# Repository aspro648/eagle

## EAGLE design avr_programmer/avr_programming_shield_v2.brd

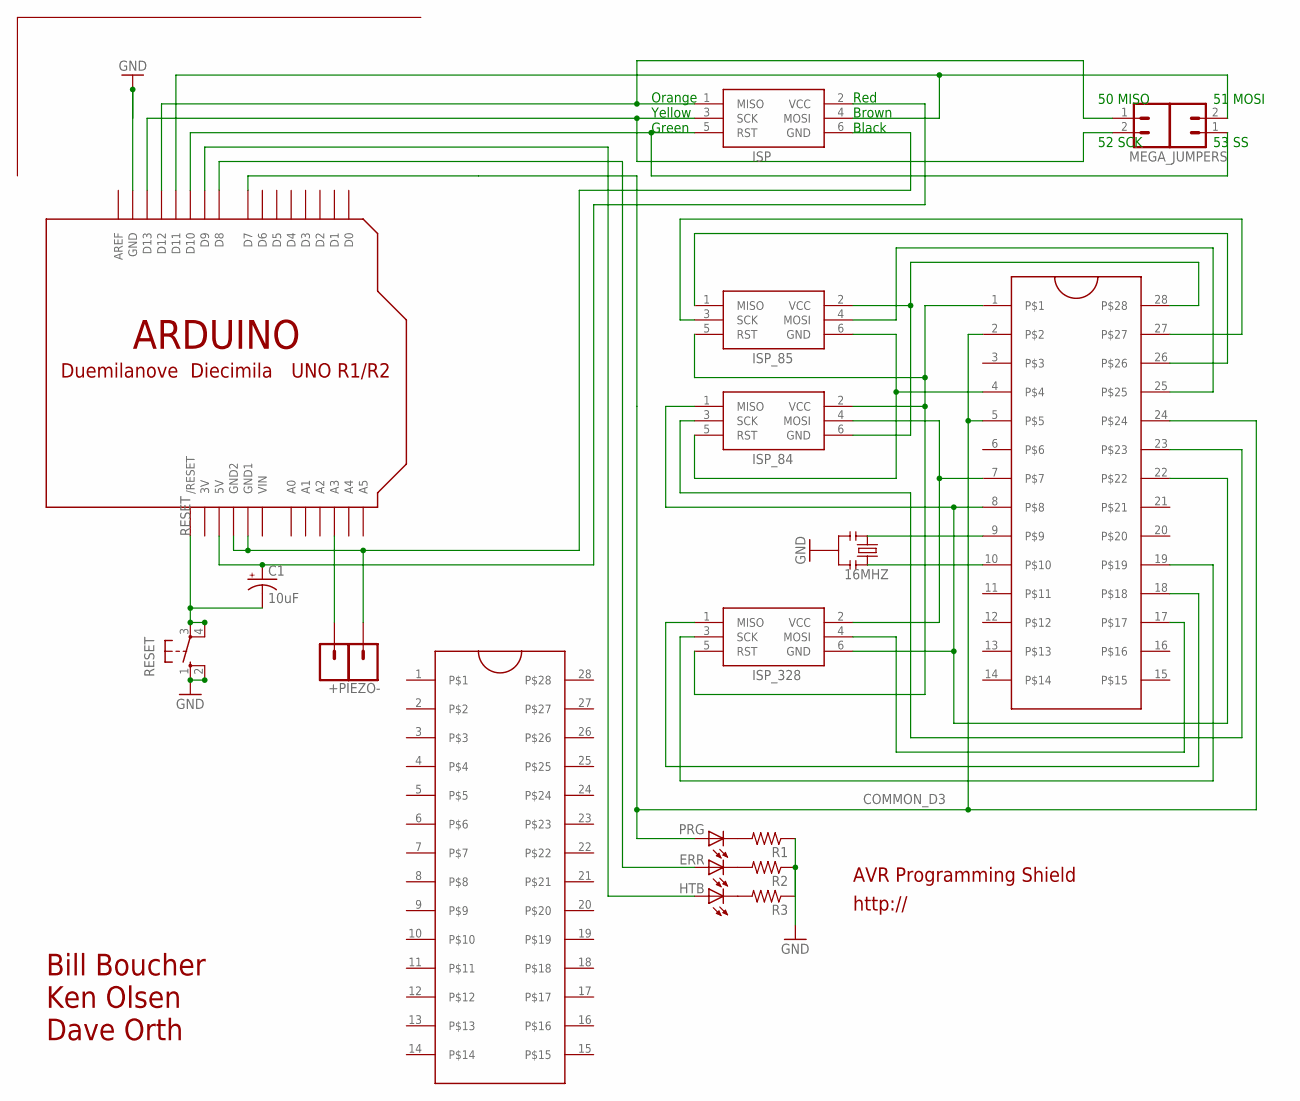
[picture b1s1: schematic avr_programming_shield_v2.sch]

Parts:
16MHZ: RESONATORPTH; RESONATOR-PTH
+PIEZO-: M01PTH; 1X01
C1: 10uF; CPOL-RADIAL-10UF-25V; MPN 106TTA035M
ERR: LED3MM
HTB: LED3MM
ISP: AVRISP-6; AVRISP
ISP_84, ISP_85, ISP_328: AVRISP-6; AVRISP
JP2: M02PTH; 1X02
JP4: M01PTH; 1X01
MEGA_JUMPERS: M02PTH; 1X02
PRG: LED3MM
R1, R2, R3: R-US_0204/2V; 0204V
RESET: 10-XX; B3F-10XX; MPN B3F-1000
U$1: ARDUINO-NOHOLE
U$3, U$4: ZIFSOCKET-28-3ZIFFSOCKET-28-3; DIL28-3-ZIF_SOCKET

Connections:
3V: U$1.3V
COMMON_D3: PRG.A, U$1.D7, U$4.2, U$4.5, U$4.24
GND: 16MHZ.2, +PIEZO-.1, ISP.6 (GND), R1.1, R2.1, R3.1, RESET.1 (S), RESET.2 (S1), U$1.GND, U$1.GND1, U$1.GND2
unnamed: ISP_328.4 (MOSI), U$4.17
unnamed: ISP.3 (SCK), MEGA_JUMPERS.2, U$1.D13
unnamed: ISP.1 (MISO), MEGA_JUMPERS.1, U$1.D12
unnamed: ISP_328.1 (MISO), U$4.18
unnamed: ISP.5 (RST), JP2.1, U$1.D10
unnamed: ISP.4 (MOSI), JP2.2, U$1.D11
unnamed: ISP_328.3 (SCK), U$4.19
unnamed: PRG.K (C), R1.2
unnamed: ERR.K (C), R2.2
unnamed: HTB.K (C), R3.2
unnamed: ISP_84.4 (MOSI), ISP_328.2 (VCC), U$4.7
unnamed: JP4.1, U$1.A3
unnamed: ISP_84.2 (VCC), ISP_85.5 (RST), ISP_328.5 (RST), U$4.1
unnamed: ISP_84.3 (SCK), U$4.23
unnamed: ISP_84.6 (GND), ISP_85.2 (VCC), U$4.28
unnamed: HTB.A, U$1.D9
unnamed: ISP_84.5 (RST), ISP_85.6 (GND), U$4.4
unnamed: ISP_85.4 (MOSI), U$4.25
unnamed: ISP_85.1 (MISO), U$4.26
unnamed: ISP_85.3 (SCK), U$4.27
unnamed: 16MHZ.1, U$4.9
unnamed: ERR.A, U$1.D8
unnamed: 16MHZ.3, U$4.10
unnamed: ISP_84.1 (MISO), ISP_328.6 (GND), U$4.8, U$4.22
RESET: C1.2 (-), RESET.3, RESET.4 (P1), U$1.RESET (/RESET)
VCC: C1.1 (+), ISP.2 (VCC), U$1.5V
VIN: U$1.VIN

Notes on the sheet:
AVR Programming Shield
http://
Red Brown Black
Orange Yellow Green
50 MISO
51 MOSI
53 SS
52 SCK
Bill Boucher Ken Olsen Dave Orth

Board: 2 copper layers, 22 parts (0 on the bottom side), 28 nets.

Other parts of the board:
E$1: OSHWLOGO_TOL_0.2
U$2: OSHWLOGO_BOTTOM

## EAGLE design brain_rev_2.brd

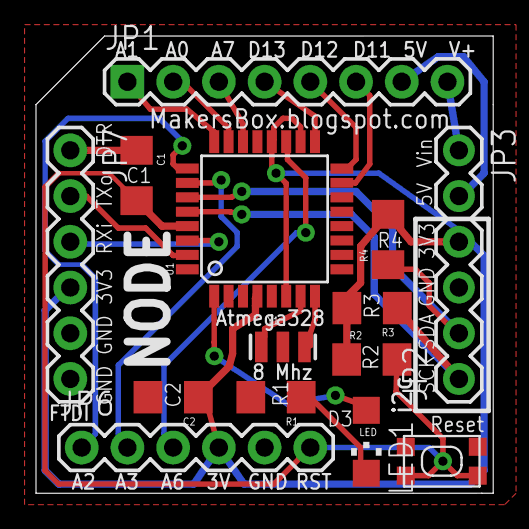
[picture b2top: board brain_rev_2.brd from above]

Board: 2 copper layers, 25.4 x 25.4 mm, 16 parts (0 on the bottom side), 23 nets.

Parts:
C1, C2: 1206
JP1: 1X08
JP2: 1X04
JP3: 1X02
JP6: 1X06
JP7: FTDI Basic; 1X06
LED1: CHIPLED_1206
R1, R2, R3, R4: 1206
SW1: SPST_TACT-KMR2; KMR2
U1: ATMEGA168; TQFP32-08
U$1: OSHWLOGO_BOTTOM
Y1: RESONATORSMD; RESONATOR-SMD

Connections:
+3V3: C2.1, JP2.4, JP6.4, JP7.4, R2.1, R3.2, R4.2, U1.4, U1.6, U1.18, U1.20
+5V: JP1.7, JP3.2
A0: JP1.2, U1.23
A1: JP1.1, U1.24
A2: JP6.1, U1.25
A3: JP6.2, U1.26
A6: JP6.3, U1.19
A7: JP1.3, U1.22
D3: LED1.A, U1.1
D11: JP1.6, U1.15
D12: JP1.5, U1.16
D13: JP1.4, U1.17
DTR: C1.1, JP7.1
GND: C2.2, JP2.3, JP6.5, JP7.5, JP7.6, R1.2, SW1.1, U1.3, U1.5, U1.21, Y1.2
unnamed: U1.8, Y1.3
unnamed: U1.7, Y1.1
unnamed: LED1.C, R1.1
RESET: C1.2, JP6.6, R2.2, SW1.2, SW1.4, U1.29
RXI: JP7.3, U1.30
SCL_A5: JP2.1, R3.1, U1.28
SDA_A4: JP2.2, R4.1, U1.27
TXO: JP7.2, U1.31
V+: JP1.8, JP3.1

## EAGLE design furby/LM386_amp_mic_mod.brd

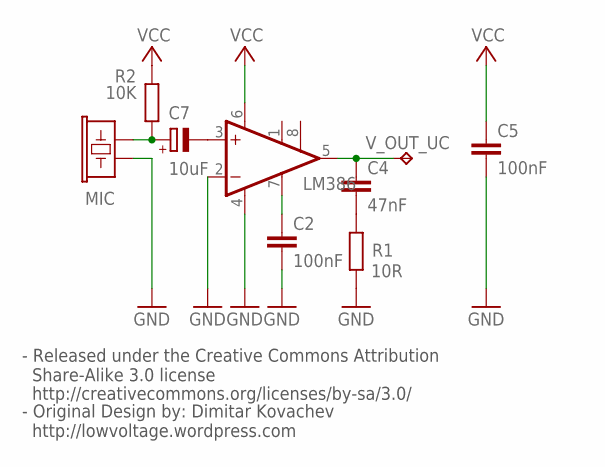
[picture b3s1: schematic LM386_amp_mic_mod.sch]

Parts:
C2: 100nF; C025-030X050
C4: 47nF; C025-030X050
C5: 100nF; C025-025X050
C7: 10uF; E2,5-6
LM386: LM386N-1; DIL08
MIC: MIC9.7MM; MIC-9.7MM
R1: 10R; 0309/12
R2: 10K; 0309/12
V_OUT_UC: TPB1,27; B1,27

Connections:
GND: C2.2, C5.2, LM386.2 (-IN), LM386.4 (GND), MIC.2, R1.2
unnamed: C4.2, R1.1
unnamed: C4.1, LM386.5 (OUT), V_OUT_UC.TP
unnamed: C2.1, LM386.7 (BYPASS)
unnamed: C7.+, MIC.1, R2.2
unnamed: C7.-, LM386.3 (+IN)
VCC: C5.1, LM386.6 (VS), R2.1

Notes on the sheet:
- Original Design by: Dimitar Kovachev http://lowvoltage.wordpress.com
- Released under the Creative Commons Attribution Share-Alike 3.0 license
http://creativecommons.org/licenses/by-sa/3.0/

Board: 2 copper layers, 9 parts (0 on the bottom side), 7 nets, no tracks yet.

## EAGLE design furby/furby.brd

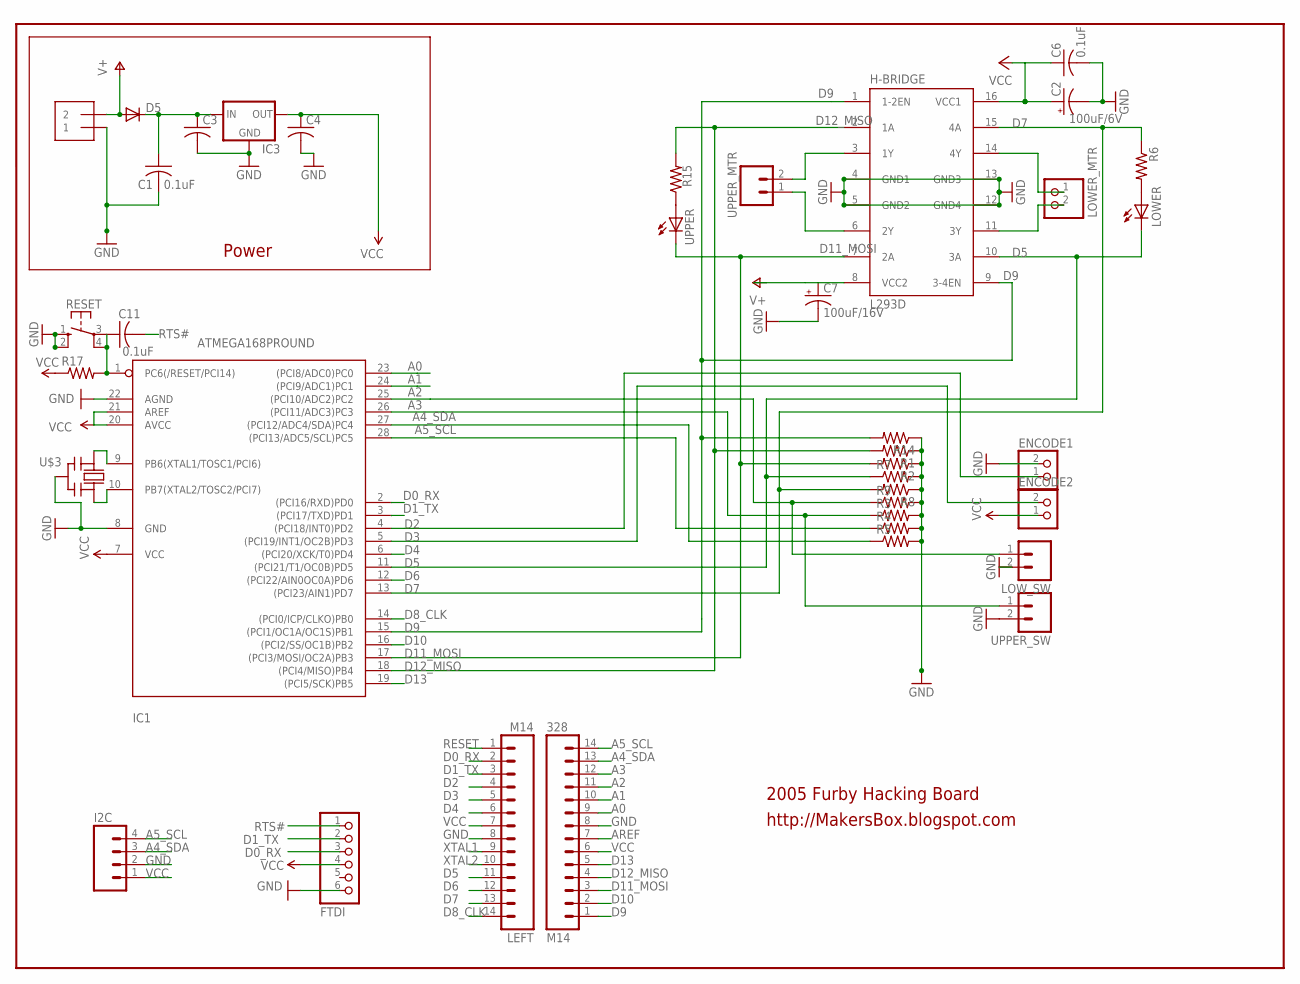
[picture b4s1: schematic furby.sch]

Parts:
328: M14; 1X14
C1, C6, C11: 0.1uF; C025-025X050
C2: 100uF/6V; E2,5-5
C3, C4: C-US025-025X050; C025-025X050
C7: 100uF/16V; E2,5-6
D5: DIODE-D-5; D-5
ENCODE1, ENCODE2: JST_2PIN-THM; JST-PH-2-THM
FTDI: FTDI; 1X06-CLEANBIG
H-BRIDGE: L293D; DIL16
I2C: M04PTH; 1X04
IC1: ATMEGA168PROUND; DIL28-3-ROUND
IC3: MCP1700INLINE; TO92-INLINE
J1: 1X2-3.5MM
LEFT: M14; 1X14
LOWER: LED3MM
LOWER_MTR: JST_2PIN-THM; JST-PH-2-THM
LOW_SW: M02PTH; 1X02
R1, R2, R3, R6, R7, R8, R9, R14, R15, R17: R-US_0207/2V; 0207/2V
R4, R5: RESISTORPTH-1/6W; 1/6W-RES
RESET: 10-XX; B3F-10XX
U$3: CERMOSCILL-THM; CERM_OSC
UPPER: LED3MM
UPPER_MTR: M02POLAR; MOLEX-1X2
UPPER_SW: M02PTH; 1X02

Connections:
A0: 328.9, IC1.23 ((PCI8/ADC0)PC0)
A1: 328.10, IC1.24 ((PCI9/ADC1)PC1)
A2: 328.11, IC1.25 ((PCI10/ADC2)PC2), LOW_SW.1, R9.1
A3: 328.12, IC1.26 ((PCI11/ADC3)PC3), R3.1, UPPER_SW.1
A4_SDA: 328.13, I2C.3, IC1.27 ((PCI12/ADC4/SDA)PC4), R5.1
A5_SCL: 328.14, I2C.4, IC1.28 ((PCI13/ADC5/SCL)PC5), R4.1
AREF: 328.7
D0_RX: FTDI.3, IC1.2 ((PCI16/RXD)PD0), LEFT.2
D1_TX: FTDI.2, IC1.3 ((PCI17/TXD)PD1), LEFT.3
D2: ENCODE1.1 (2), IC1.4 ((PCI18/INT0)PD2), LEFT.4
D3: ENCODE2.2 (1), IC1.5 ((PCI19/INT1/OC2B)PD3), LEFT.5
D4: IC1.6 ((PCI20/XCK/T0)PD4), LEFT.6
D5: H-BRIDGE.10 (3A), IC1.11 ((PCI21/T1/OC0B)PD5), LEFT.11, LOWER.K (C), R7.1
D6: IC1.12 ((PCI22/AIN0OC0A)PD6), LEFT.12
D7: H-BRIDGE.15 (4A), IC1.13 ((PCI23/AIN1)PD7), LEFT.13, R6.1, R8.2
D8_CLK: IC1.14 ((PCI0/ICP/CLKO)PB0), LEFT.14
D9: 328.1, H-BRIDGE.1 (1-2EN), H-BRIDGE.9 (3-4EN), IC1.15 ((PCI1/OC1A/OC1S)PB1), R14.2
D10: 328.2, IC1.16 ((PCI2/SS/OC1B)PB2)
D11_MOSI: 328.3, H-BRIDGE.7 (2A), IC1.17 ((PCI3/MOSI/OC2A)PB3), R2.2, UPPER.K (C)
D12_MISO: 328.4, H-BRIDGE.2 (1A), IC1.18 ((PCI4/MISO)PB4), R1.2, R15.2
D13: 328.5, IC1.19 ((PCI5/SCK)PB5)
GND: 328.8, C1.2, C2.-, C3.2, C4.2, C6.2, C7.-, ENCODE1.2 (1), FTDI.6, H-BRIDGE.4 (GND1), H-BRIDGE.5 (GND2), H-BRIDGE.12 (GND4), H-BRIDGE.13 (GND3), I2C.2, IC1.8 (GND), IC1.22 (AGND), IC3.1 (GND), J1.1, LEFT.8, LOW_SW.2, R1.1, R2.1, R3.2, R4.2, R5.2, R7.2, R8.1, R9.2, R14.1, RESET.1 (S), RESET.2 (S1), U$3.P$2 (GND), UPPER_SW.2
unnamed: H-BRIDGE.11 (3Y), LOWER_MTR.2 (1)
unnamed: LOWER.A, R6.2
unnamed: R15.1, UPPER.A
unnamed: H-BRIDGE.14 (4Y), LOWER_MTR.1 (2)
unnamed: C1.1, C3.1, D5.C, IC3.2 (IN)
unnamed: H-BRIDGE.3 (1Y), UPPER_MTR.2
unnamed: H-BRIDGE.6 (2Y), UPPER_MTR.1
RESET: C11.1, IC1.1 (PC6(/RESET/PCI14)), LEFT.1, R17.2, RESET.3, RESET.4 (P1)
RTS#: C11.2, FTDI.1
V+: C7.+, D5.A, H-BRIDGE.8 (VCC2), J1.2
VCC: 328.6, C2.+, C4.1, C6.1, ENCODE2.1 (2), FTDI.4, H-BRIDGE.16 (VCC1), I2C.1, IC1.7 (VCC), IC1.20 (AVCC), IC1.21 (AREF), IC3.3 (OUT), LEFT.7, R17.1
XTAL1: IC1.9 (PB6(XTAL1/TOSC1/PCI6)), LEFT.9, U$3.P$1 (IN)
XTAL2: IC1.10 (PB7(XTAL2/TOSC2/PCI7)), LEFT.10, U$3.P$3 (OUT)

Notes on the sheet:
2005 Furby Hacking Board
http://MakersBox.blogspot.com
Power

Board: 2 copper layers, 38 parts (0 on the bottom side), 34 nets, no tracks yet.

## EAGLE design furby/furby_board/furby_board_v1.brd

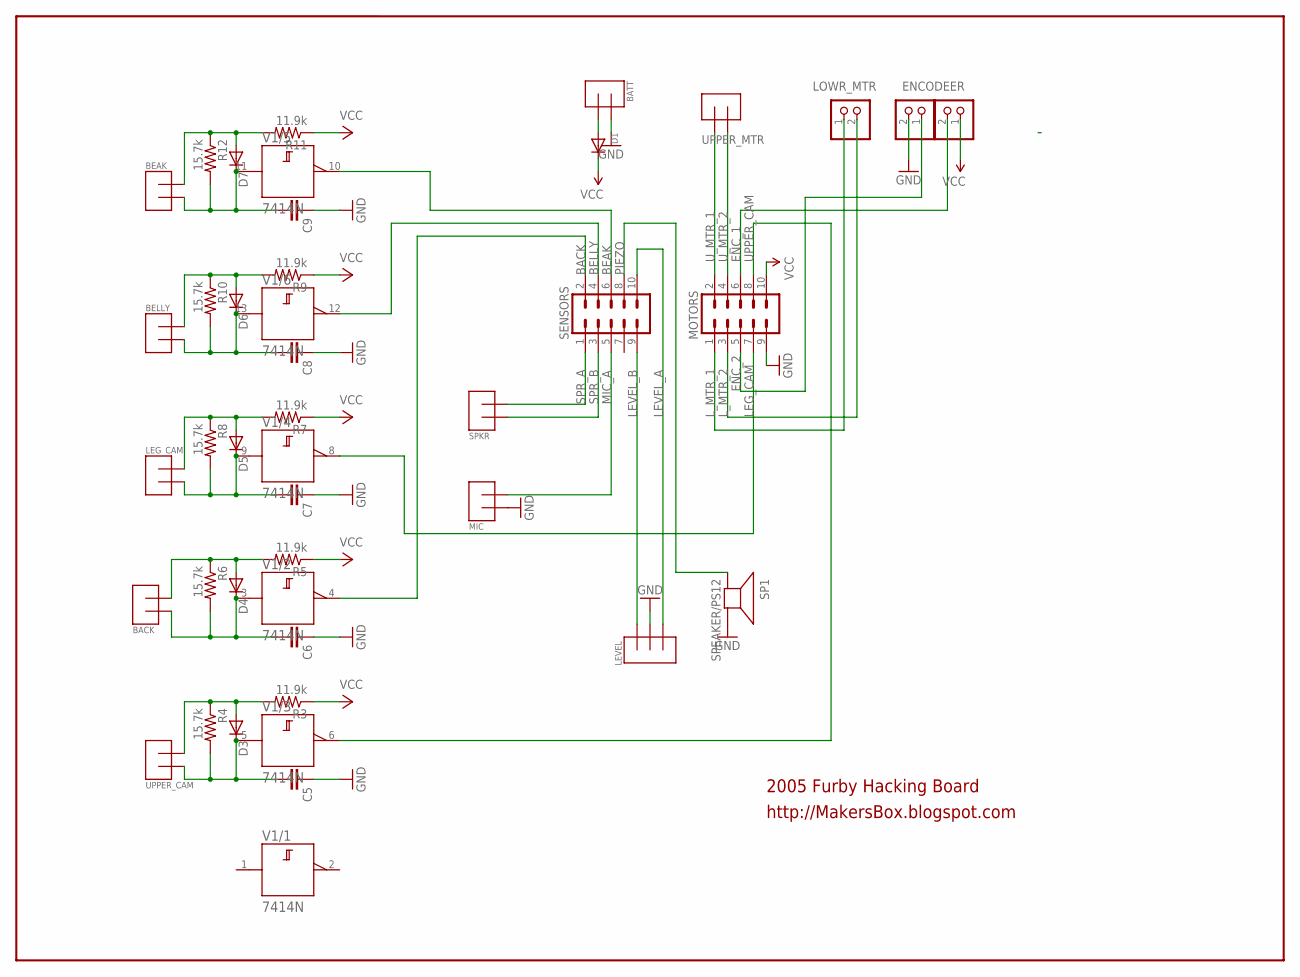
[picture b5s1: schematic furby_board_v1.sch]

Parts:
BACK: TERMINAL2; TERMINAL_2
BATT: TERMINAL2; TERMINAL_2
BEAK: TERMINAL2; TERMINAL_2
BELLY: TERMINAL2; TERMINAL_2
C5, C6, C7, C8, C9: CAPPTH; CAP-PTH-SMALL
D1: DIODEDO-1N4148; DO-1N4148
D3, D4, D5, D6, D7: DIODE-D-2.5; D-2.5
ENCODE2: JST_2PIN-THM; JST-PH-2-THM
ENCODEER: JST_2PIN-THM; JST-PH-2-THM
LEG_CAM: TERMINAL2; TERMINAL_2
LEVEL: TERMINAL; TERMINAL_3
LOWR_MTR: JST_2PIN-THM; JST-PH-2-THM
MIC: TERMINAL2; TERMINAL_2
MOTORS: M05X2SHD; 2X5-SHROUDED
R3, R5, R7, R9, R11: 11.9k; 0204V
R4, R6, R8, R10, R12: 15.7k; 0204V
SENSORS: M05X2SHD; 2X5-SHROUDED
SP1: SPEAKER/PS12; PS12
SPKR: TERMINAL2; TERMINAL_2
UPPER_CAM: TERMINAL2; TERMINAL_2
UPPER_MTR: TERMINAL2; TERMINAL_2
V1: 7414N; DIL14

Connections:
+UB: V1.14 (+UB)
-UB: V1.7 (-UB)
BACK: SENSORS.2, V1.4 (Y)
BEAK: SENSORS.6, V1.10 (Y)
BELLY: SENSORS.4, V1.12 (Y)
ENC_1: ENCODE2.2 (1), MOTORS.6
ENC_2: ENCODEER.1 (2), MOTORS.5
GND: BATT.P$1, C5.1, C6.1, C7.1, C8.1, C9.1, ENCODEER.2 (1), LEVEL.P$2, MIC.P$1, MOTORS.9, SP1.P$2 (-)
LEG_CAM: MOTORS.7, V1.8 (Y)
LEVEL_A: LEVEL.P$3, SENSORS.10
LEVEL_B: LEVEL.P$1, SENSORS.9
L_MTR_1: LOWR_MTR.1 (2), MOTORS.1
L_MTR_2: LOWR_MTR.2 (1), MOTORS.3
MIC_A: MIC.P$2, SENSORS.5
unnamed: BATT.P$2, D1.A
unnamed: D3.A, R3.2, R4.1, UPPER_CAM.P$2
unnamed: C5.2, D3.C, R4.2, UPPER_CAM.P$1, V1.5 (A)
unnamed: BACK.P$2, D4.A, R5.2, R6.1
unnamed: BACK.P$1, C6.2, D4.C, R6.2, V1.3 (A)
unnamed: D5.A, LEG_CAM.P$1, R7.2, R8.1
unnamed: C7.2, D5.C, LEG_CAM.P$2, R8.2, V1.9 (A)
unnamed: BELLY.P$1, D6.A, R9.2, R10.1
unnamed: BELLY.P$2, C8.2, D6.C, R10.2, V1.13 (A)
unnamed: BEAK.P$1, D7.A, R11.2, R12.1
unnamed: BEAK.P$2, C9.2, D7.C, R12.2, V1.11 (A)
PIEZO: SENSORS.8, SP1.P$1 (+)
SPR_A: SENSORS.1, SPKR.P$2
SPR_B: SENSORS.3, SPKR.P$1
UPPER_CAM: MOTORS.8, V1.6 (Y)
U_MTR_1: MOTORS.2, UPPER_MTR.P$1
U_MTR_2: MOTORS.4, UPPER_MTR.P$2
VCC: D1.C, ENCODE2.1 (2), MOTORS.10, R3.1, R5.1, R7.1, R9.1, R11.1

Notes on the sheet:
2005 Furby Hacking Board
http://MakersBox.blogspot.com

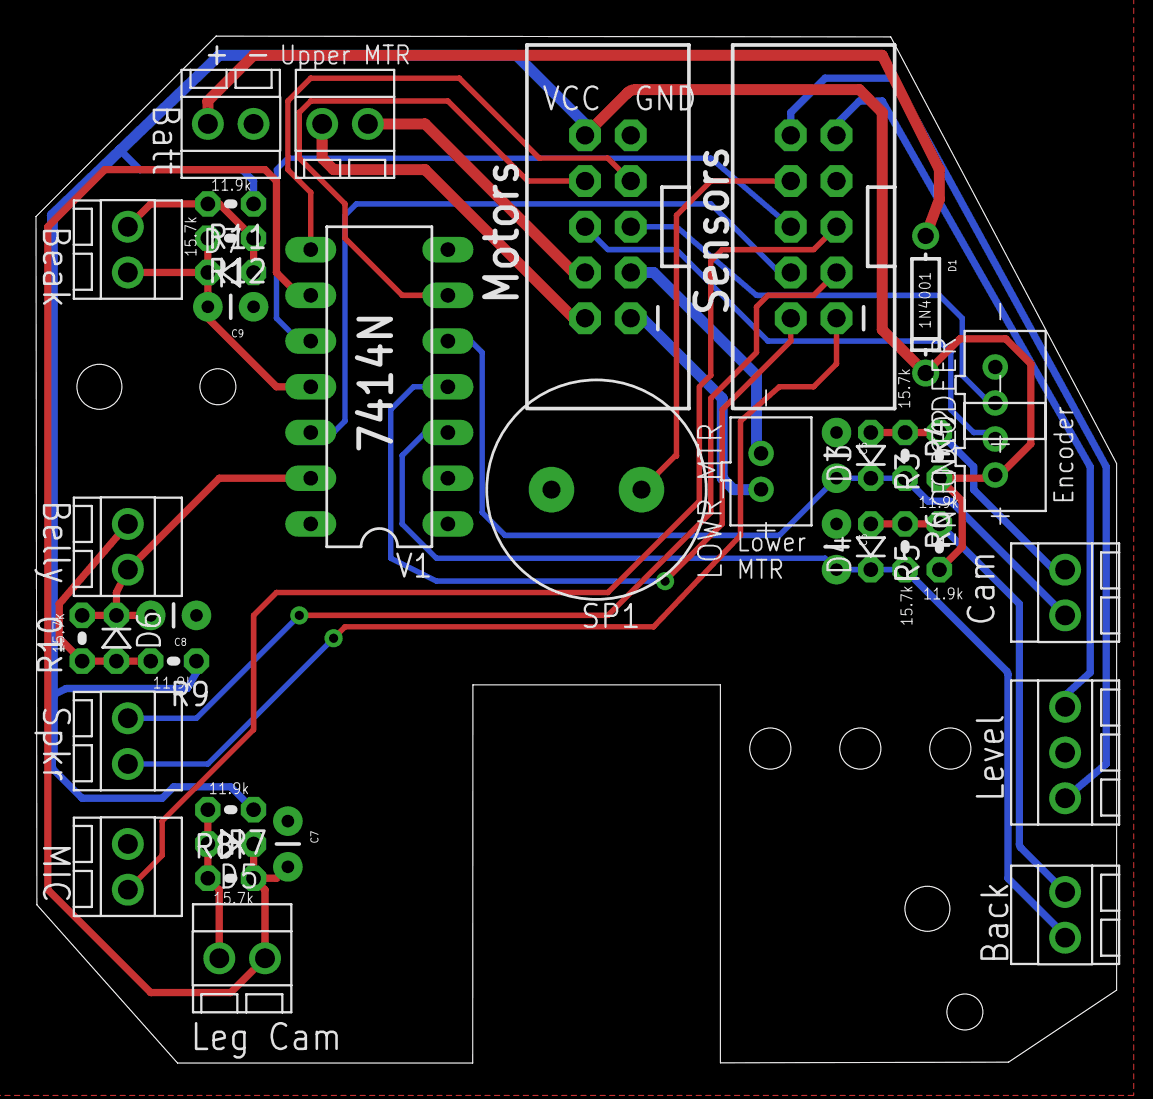
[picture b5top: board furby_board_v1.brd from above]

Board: 2 copper layers, 60.0 x 57.1 mm, 38 parts (0 on the bottom side), 30 nets.

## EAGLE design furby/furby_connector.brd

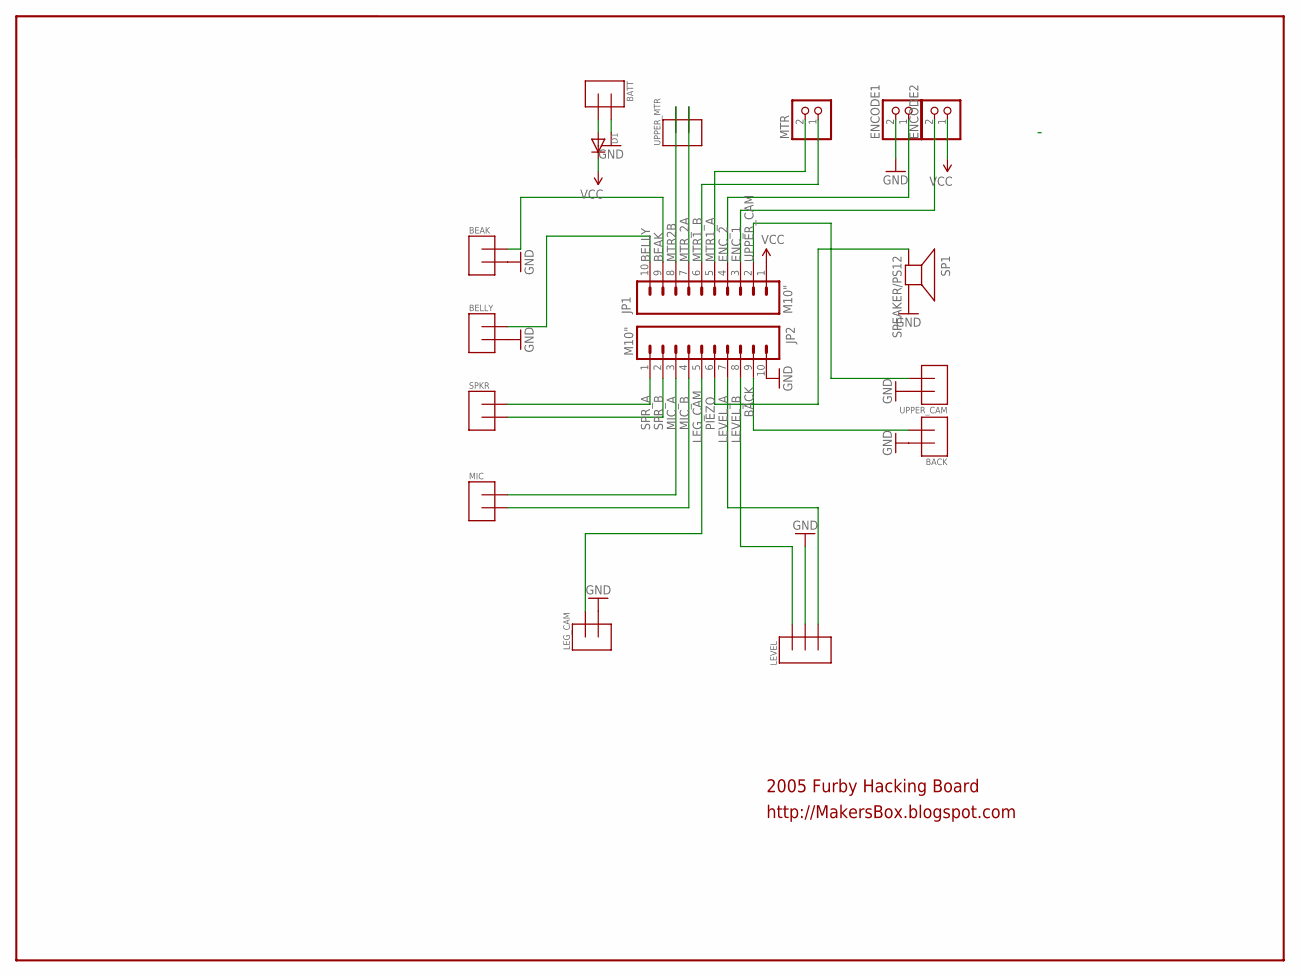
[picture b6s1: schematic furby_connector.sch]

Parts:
BACK: TERMINAL2; TERMINAL_2
BATT: TERMINAL2; TERMINAL_2
BEAK: TERMINAL2; TERMINAL_2
BELLY: TERMINAL2; TERMINAL_2
D1: DIODEDO-1N4148; DO-1N4148
ENCODE1, ENCODE2: JST_2PIN-THM; JST-PH-2-THM
JP1, JP2: M10"; 1X10
LEG_CAM: TERMINAL2; TERMINAL_2
LEVEL: TERMINAL; TERMINAL_3
MIC: TERMINAL2; TERMINAL_2
MTR: JST_2PIN-THM; JST-PH-2-THM
SP1: SPEAKER/PS12; PS12
SPKR: TERMINAL2; TERMINAL_2
UPPER_CAM: TERMINAL2; TERMINAL_2
UPPER_MTR: TERMINAL2; TERMINAL_2

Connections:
BACK: BACK.P$2, JP2.9
BEAK: BEAK.P$1, JP1.9
BELLY: BELLY.P$1, JP1.10
ENC_1: ENCODE2.2 (1), JP1.3
ENC_2: ENCODE1.1 (2), JP1.4
GND: BACK.P$1, BATT.P$1, BEAK.P$2, BELLY.P$2, ENCODE1.2 (1), JP2.10, LEG_CAM.P$2, LEVEL.P$2, SP1.P$2 (-), UPPER_CAM.P$1
LEG_CAM: JP2.5, LEG_CAM.P$1
LEVEL_A: JP2.7, LEVEL.P$3
LEVEL_B: JP2.8, LEVEL.P$1
MIC_A: JP2.3, MIC.P$1
MIC_B: JP2.4, MIC.P$2
MTR1_A: JP1.5, MTR.2 (1)
MTR1_B: JP1.6, MTR.1 (2)
MTR2B: JP1.8, UPPER_MTR.P$1
MTR_2A: JP1.7, UPPER_MTR.P$2
unnamed: BATT.P$2, D1.A
PIEZO: JP2.6, SP1.P$1 (+)
SPR_A: JP2.1, SPKR.P$1
SPR_B: JP2.2, SPKR.P$2
UPPER_CAM: JP1.2, UPPER_CAM.P$2
VCC: D1.C, ENCODE2.1 (2), JP1.1

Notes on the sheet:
2005 Furby Hacking Board
http://MakersBox.blogspot.com

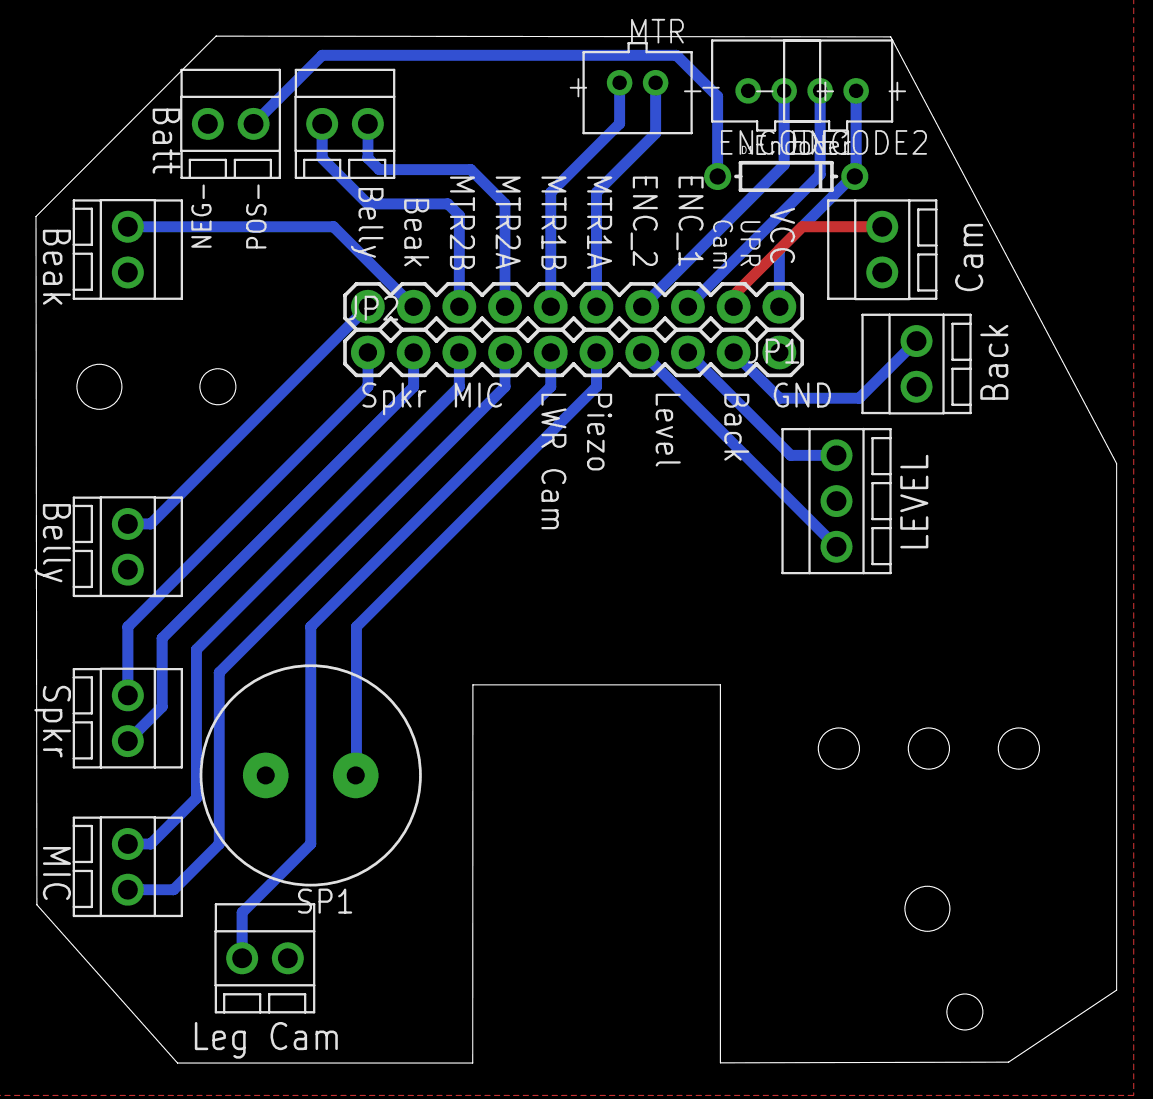
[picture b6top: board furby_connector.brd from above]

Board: 2 copper layers, 60.0 x 57.1 mm, 17 parts (0 on the bottom side), 21 nets.

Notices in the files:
parts and their libraries:
SparkFun: Licensing: CC v3.0 Share-Alike You are welcome to use this library for commercial purposes.
